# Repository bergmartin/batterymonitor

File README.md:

# ESP32 Battery Voltage Monitor

A PlatformIO project for monitoring 12V battery voltage using an ESP32 microcontroller with **ultra-low power consumption** through deep sleep mode.

## 🌟 Key Features

- **Ultra-Low Power:** Deep sleep mode with only 0.12-0.23 mA average draw (99.8% power reduction!)
- **Long Battery Life:** Monitor can run for years on the battery it's monitoring
- **MQTT Integration:** Publish readings to MQTT broker for remote monitoring (Home Assistant, Node-RED, etc.)
- **OLED Display:** SH1106 128x64 display shows battery voltage, percentage, status, and WiFi signal strength
- Real-time 12V battery voltage monitoring
- Support for **Lead-Acid** and **LiFePO4** battery types
- Battery type configured at build time
- Battery percentage calculation with type-specific thresholds
- Battery status indicators (FULL, GOOD, LOW_BATTERY, CRITICAL, DEAD)
- Visual battery level display with progress bar
- WiFi signal strength indicator
- Low battery warnings
- Averaged ADC readings for accuracy
- RTC memory for persistent data across sleep cycles
- **3D Printable Enclosure** for professional deployment

## ⚡ Power Consumption

| Mode | Current Draw | Battery Life (100Ah) |
|------|-------------|---------------------|
| **Deep Sleep (default)** | 0.12-0.23 mA | **50-95 years** 🎉 |
| Continuous monitoring | 80-160 mA | 26-52 days |

**Deep sleep mode draws less power than the battery loses naturally!**

See [DEEP_SLEEP.md](doc/DEEP_SLEEP.md) for detailed power analysis.

## Hardware Requirements

### Components
- ESP32 development board
- 12V battery
- 100kΩ resistor (R1)
- 22kΩ resistor (R2)
- SH1106 OLED Display (128x64, I2C) - optional but recommended
- Connecting wires

### Circuit Diagram

```
12V Battery (+) ----[100kΩ]----+----[22kΩ]---- GND
                               |
                          GPIO34 (ADC)
                          ESP32
```

### Voltage Divider Explanation

The ESP32 ADC can only read voltages up to 3.3V. To safely measure a 12V battery (and up to 14.6V for LiFePO4), we use a voltage divider:

- **R1** (100kΩ) + **R2** (22kΩ) creates a 5.55:1 ratio
- 12V battery voltage becomes ~2.16V at the ADC pin
- Formula: `V_ADC = V_Battery × (R2 / (R1 + R2))`
- Result: `V_ADC = 12V × (22kΩ / 122kΩ) = 2.16V`

## Wiring Instructions

1. **Connect Voltage Divider:**
   - Solder 100kΩ resistor (R1) to battery positive terminal
   - Connect 22kΩ resistor (R2) between the junction and GND
   - Connect junction point to GPIO34 on ESP32

2. **Ground Connection:**
   - Connect battery negative terminal to ESP32 GND

3. **Power ESP32:**
   - Power the ESP32 via USB or separate power supply
   - **Important:** Do NOT power ESP32 directly from the 12V battery without a voltage regulator

## Software Setup

### Installation

1. Install [PlatformIO](https://platformio.org/)
2. Clone or download this project
3. Open the project in VS Code with PlatformIO extension

### MQTT Configuration (Optional)

To enable remote monitoring via MQTT:

1. **Configure WiFi credentials:**
   ```bash
   cd include/
   cp wifi_credentials.h.example wifi_credentials.h
   # Edit wifi_credentials.h with your WiFi SSID and password
   ```

2. **Configure MQTT broker:**
   ```bash
   cp mqtt_credentials.h.example mqtt_credentials.h
   # Edit mqtt_credentials.h with your MQTT broker details
   ```

3. **See [MQTT.md](doc/MQTT.md) for complete MQTT setup guide**, including:
   - MQTT broker options (Mosquitto, CloudMQTT, Home Assistant)
   - Topic structure and JSON format
   - Home Assistant integration
   - Testing and troubleshooting

### Build and Upload

**Default (Lead-Acid battery):**
```bash
# Build the project
pio run

# Upload to ESP32
pio run --target upload

# Monitor serial output
pio device monitor
```

**For LiFePO4 battery:**
```bash
# Build for LiFePO4
pio run -e esp32dev -D BATTERY_TYPE=BATTERY_TYPE_LIFEPO4

# Upload to ESP32
pio run -e esp32dev -D BATTERY_TYPE=BATTERY_TYPE_LIFEPO4 --target upload

# Monitor serial output
pio device monitor
```

**Alternative: Edit platformio.ini**

Change the build flag in the default `[env:esp32dev]` section:
```ini
build_flags = 
  -D BATTERY_TYPE=BATTERY_TYPE_LIFEPO4  ; Options: BATTERY_TYPE_LEAD_ACID or BATTERY_TYPE_LIFEPO4
```

Or use PlatformIO IDE buttons in VS Code.

## Testing

The project includes comprehensive unit tests for all battery monitoring logic.

### Run Tests

**Test Lead-Acid configuration:**
```bash
pio test -e esp32dev
```

**Test LiFePO4 configuration:**
```bash
pio test -e esp32dev -D BATTERY_TYPE=BATTERY_TYPE_LIFEPO4
```

**Test both configurations:**
```bash
pio test
```

The tests cover:
- Battery percentage calculations
- Battery status determination
- ADC to voltage conversion
- Voltage divider safety
- Edge cases and boundary conditions

See `test/README.md` for detailed testing documentation.

## Configuration

### Battery Type Selection

The project supports two battery types, configured at **build time**:

**Option 1: Use the default environment with build flag**
- `esp32dev` with default `BATTERY_TYPE_LEAD_ACID` build flag
- `esp32dev` with `-D BATTERY_TYPE=BATTERY_TYPE_LIFEPO4` build flag for LiFePO4

**Option 2: Edit the default environment**

In `platformio.ini`, modify the build_flags:
```ini
[env:esp32dev]
build_flags = 
  -D BATTERY_TYPE=LEAD_ACID  ; or LIFEPO4
```

### Voltage Thresholds

The voltage thresholds are automatically set based on battery type:

**Lead-Acid (12V):**
- Full: 12.7V
- Nominal: 12.4V (75%)
- Low: 12.0V (25%)
- Critical: 11.8V
- Minimum: 10.5V

**LiFePO4 (12V nominal, 4S configuration):**
- Full: 14.6V
- Nominal: 13.2V (75%)
- Low: 12.8V (25%)
- Critical: 12.0V
- Minimum: 10.0V

### Other Adjustable Parameters

You can adjust these parameters in `lib/BatteryMonitor/battery_config.h` (in the `Config` namespace):

```cpp
constexpr int BATTERY_ADC_PIN = 34;           // ADC pin (GPIO34)
constexpr float VOLTAGE_DIVIDER_RATIO = 5.545;  // Adjust if using different resistors
constexpr unsigned long READING_INTERVAL_MS = 10000;  // Reading interval (active mode, 10 seconds)
constexpr uint64_t DEEP_SLEEP_INTERVAL_US = 3600000000ULL;  // Deep sleep interval (1 hour)
```

### For Different Resistor Values

If you use different resistors, calculate the voltage divider ratio:

```
VOLTAGE_DIVIDER_RATIO = (R1 + R2) / R2
```

Example:
- R1 = 100kΩ, R2 = 33kΩ → Ratio = 4.03
- R1 = 20kΩ, R2 = 10kΩ → Ratio = 3.0

## Serial Output Example

**Lead-Acid Battery:**
```
=================================
ESP32 Battery Voltage Monitor
=================================
Battery Type: Lead-Acid
Voltage Range: 10.5V - 12.7V

─────────────────────────────────
Battery Voltage: 12.45 V
Battery Level:   88.6 %
Status:          GOOD
Battery: [████████░░]
```

**LiFePO4 Battery:**
```
=================================
ESP32 Battery Voltage Monitor
=================================
Battery Type: LiFePO4
Voltage Range: 10.0V - 14.6V

─────────────────────────────────
Battery Voltage: 13.84 V
Battery Level:   83.5 %
Status:          GOOD
Battery: [████████░░]
```

## Battery Voltage Guidelines

The project automatically configures voltage thresholds based on your battery type selection.

### Lead-Acid Batteries (12V)
- **12.7V** - Fully charged (100%)
- **12.4V** - 75% charged
- **12.2V** - 50% charged
- **12.0V** - 25% charged
- **11.8V** - Discharged (should recharge)
- **10.5V** - Minimum safe voltage

### LiFePO4 Batteries (12V nominal, 4S configuration)
- **14.6V** - Fully charged (100%) - 4 × 3.65V
- **13.6V** - 90% charged
- **13.2V** - 75% charged
- **13.0V** - 50% charged
- **12.8V** - 25% charged
- **12.0V** - Discharged (should recharge)
- **10.0V** - Minimum safe voltage - 4 × 2.5V

**Note:** LiFePO4 batteries have a flatter discharge curve than lead-acid, maintaining voltage better under load.

## Safety Notes

⚠️ **Important Safety Information:**

1. **Never exceed ADC input voltage:** Ensure your voltage divider outputs max 3.0V
2. **Double-check connections:** Incorrect wiring can damage your ESP32
3. **Use proper resistor wattage:** 1/4W resistors are typically sufficient
4. **Battery polarity:** Connect positive to R1, negative to GND
5. **Isolated ground:** If powering ESP32 separately, ensure common ground with battery

## Calibration

For more accurate readings, you can calibrate the system:

1. Measure actual battery voltage with a multimeter
2. Compare with ESP32 reading
3. Adjust the `VOLTAGE_DIVIDER_RATIO` constant if needed
4. The ADC may have slight variations; fine-tune the ratio for accuracy

## Troubleshooting

**Reading shows 0V:**
- Check voltage divider connections
- Verify GPIO34 is connected to the junction point
- Check resistor values

**Reading too high/low:**
- Verify resistor values (use multimeter)
- Recalculate voltage divider ratio
- Check for loose connections

**Unstable readings:**
- Increase SAMPLES count for more averaging
- Add a small capacitor (0.1µF) across R2
- Check for electromagnetic interference

**MQTT not connecting:**
- See [MQTT.md](doc/MQTT.md) troubleshooting section
- Verify WiFi credentials in `include/wifi_credentials.h`
- Check MQTT broker is accessible and credentials are correct
- Test broker with mosquitto-clients: `mosquitto_sub -h broker -t "#"`

## Documentation

- **[WIRING.md](doc/WIRING.md)** - Detailed wiring instructions with buck converter setup
- **[DISPLAY.md](doc/DISPLAY.md)** - SH1106 OLED display wiring and configuration
- **[DEEP_SLEEP.md](doc/DEEP_SLEEP.md)** - Deep sleep implementation and power analysis
- **[MQTT.md](doc/MQTT.md)** - MQTT setup, configuration, and integration guide
- **[OTA.md](doc/OTA.md)** - Over-the-Air update setup and usage
- **[REFACTORING.md](doc/REFACTORING.md)** - Code structure and refactoring documentation
- **[AGENTS.md](doc/AGENTS.md)** - AI assistant context and best practices
- **[test/README.md](test/README.md)** - Testing framework and test documentation
- **[enclosure/README.md](enclosure/README.md)** - 3D printable enclosure guide

## License

MIT License - Feel free to modify and use in your projects.

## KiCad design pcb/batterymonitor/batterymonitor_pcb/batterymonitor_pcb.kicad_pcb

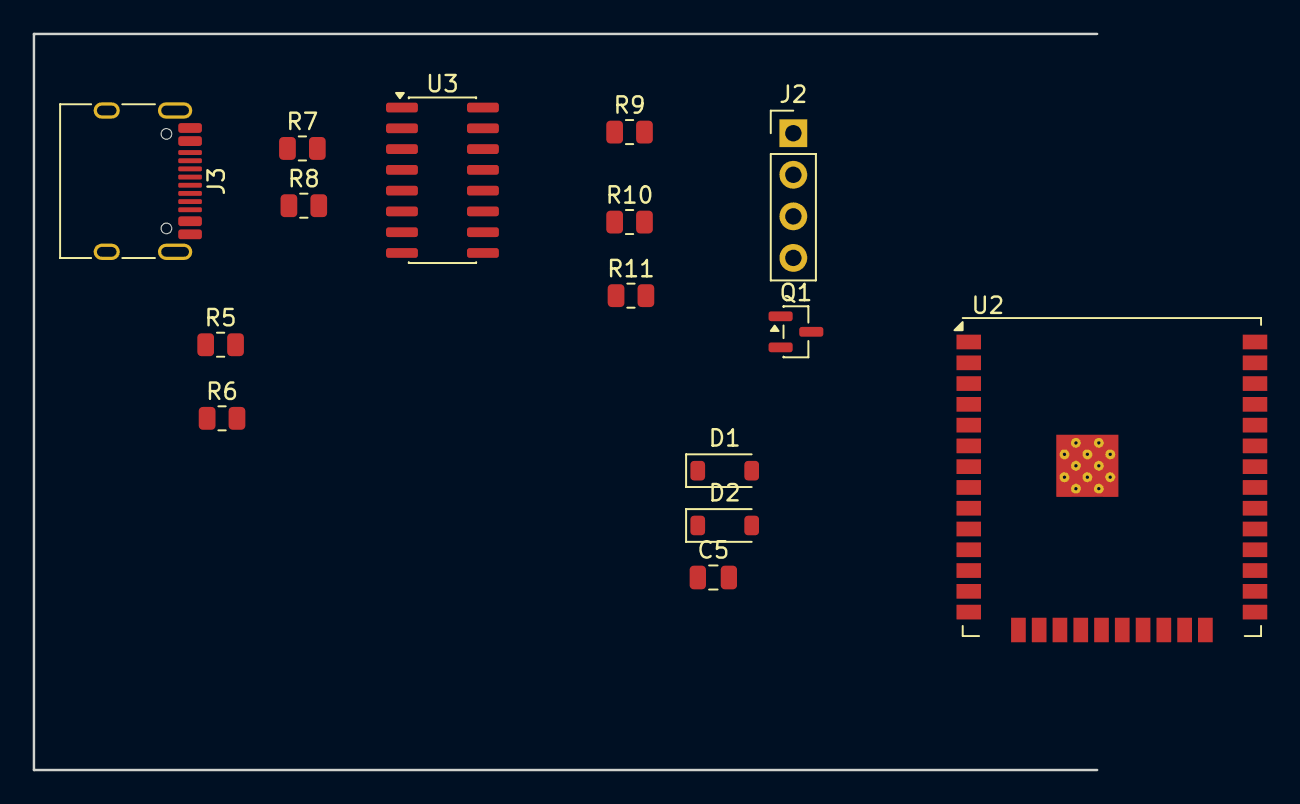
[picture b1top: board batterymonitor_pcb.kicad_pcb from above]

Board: 2 copper layers, 65.0 x 45.0 mm, 15 parts (0 on the bottom side), 17 nets, no tracks yet.

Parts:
C5: 100nF/10V; C_0805_2012Metric
D1, D2: SS14; D_SOD-123
J2: Conn_01x04_Pin; PinHeader_1x04_P2.54mm_Vertical
J3: USB_C_Receptacle_HRO_TYPE-C-31-M-12
Q1: S8050; SOT-23
R5, R6: 1k; R_0805_2012Metric
R7, R8: 5.1k; R_0805_2012Metric
R9, R10, R11: 10k; R_0805_2012Metric
U2: ESP32-WROOM-32U-N4; ESP32-WROOM-32U
U3: CH340C; SOIC-16_3.9x9.9mm_P1.27mm

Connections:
/3.3V: C5.1, J2.1, R11.1, U2.2 (3V3), U3.5 (VCC), U3.6 (V3)
/12V: D1.1 (K), D2.1 (K)
/ESP_EN: Q1.3 (C), R11.2, U2.3 (EN)
/ESP_RXD: R5.2, U2.34 (RXD0)
/ESP_TXD: R6.1, U2.35 (TXD0), U3.8 (RXD)
/GND: C5.2, J2.2, J3.A1 (GND), J3.B12 (GND), J3.SH (SHIELD), R7.2, R8.2, U2.1 (GND), U2.15 (GND), U2.38 (GND), U3.3 (GND)
/SCL: J2.3, U2.36 (GPIO22)
/SDA: J2.4, U2.33 (GPIO21)
/USB_CC1: J3.A5 (CC1), R7.1
/USB_CC2: J3.B5 (CC2), R8.1
/USB_DN: J3.A7 (D-), J3.B7 (D-), U3.2 (UD-)
/USB_DP: J3.A6 (D+), J3.B6 (D+), U3.1 (UD+)
/USB_DTR: Q1.2 (E), R10.2, U3.9 (DTR)
/USB_RTS: R9.2, U3.14 (RTS)
/VBUS: D2.2 (A), J3.A4 (VBUS), J3.B9 (VBUS)
unnamed: Q1.1 (B), R9.1
unnamed: R5.1, U3.7 (TXD)

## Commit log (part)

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2025-12-09 Add ESP32 battery monitor with Lead-Acid and LiFePO4 support
2025-12-10 Add comprehensive unit tests and refactor code into library
    - Created BatteryMonitor library with battery_monitor.h/cpp
    - Refactored shared functions (calculateBatteryPercentage, getBatteryStatus, adcToBatteryVoltage)
    - Added 32 unit tests covering:
    - Battery percentage calculations
    - Battery status determination
    - ADC to voltage conversion
2025-12-10 Add comprehensive refactoring documentation
2025-12-11 Update README with deep sleep power features
    Highlight ultra-low power consumption in main README:
    - Power consumption comparison table
    - Link to detailed DEEP_SLEEP.md documentation
    - Emphasize power efficiency as key feature
2025-12-11 Add comprehensive wiring guide and hardware documentation
    Complete hardware setup documentation:
    - Detailed wiring diagrams with ASCII art
    - Component list with specifications
    - Step-by-step connection instructions
    - Pin configuration reference
    - Wire gauge recommendations
2025-12-11 adding satl files to gitignore
2025-12-13 Add MQTT publishing for remote battery monitoring
    Implemented MQTT functionality to publish battery readings to an MQTT broker:
    Features:
    - WiFi connection with configurable timeout
    - MQTT client using PubSubClient library
    - Publishes voltage, percentage, status, type, boot count
    - JSON topic with all data + WiFi RSSI
2025-12-13 Update config and MQTT publishing logic
    - Tweak WiFi/MQTT timeouts and configuration in battery_config.h
    - Adjust MQTT publish flow in main.cpp for reliability and power
    - Prep for remote monitoring with retained JSON payloads
2025-12-13 remove useless readme files
2025-12-15 feat: serial deep-sleep controls and first-boot delay
    - Add serial commands: 'nosleep'/'sleep' and 'set deep_sleep <on|off>'
    - Persist deep sleep setting in NVS via ConfigManager
    - Wait 30s before first deep sleep to allow serial config
    - Update release workflow notes re: NVS defaults
    - Update VS Code includes for ConfigManager/Preferences
2025-12-15 refactor: extract manager classes for better separation of concerns
    - Create NetworkManager class (224 lines)
    - WiFi and MQTT connection management
    - Callback system for OTA and reset triggers
    - Publishing and disconnect handling
    - Create OTAManager class (214 lines)
    - ArduinoOTA and HTTP update handling
2025-12-15 refactor: separate manager implementations from headers
    - Split NetworkManager into network_manager.h (38 lines) and network_manager.cpp (213 lines)
    - Split OTAManager into ota_manager.h (36 lines) and ota_manager.cpp (210 lines)
    - Split CommandHandler into command_handler.h (24 lines) and command_handler.cpp (205 lines)
    - Follows C++ best practices for interface/implementation separation
    - Improves compilation times (changes to .cpp don't require recompiling dependents)
    - Maintains all functionality with cleaner, more maintainable code structure
2025-12-16 feat: Add DHCP support, persistent OTA triggers, and automatic update checking
    - Switch from static IP to DHCP by default (configurable via USE_STATIC_IP flag)
    - Implement persistent OTA trigger storage across deep sleep cycles using ESP32 Preferences
    - Add automatic version checking on every wake cycle
    - Firmware now checks GitHub for newer versions and auto-updates when available
    - OTA updates triggered via MQTT are now persisted and processed on next boot
    - Add version tracking (FIRMWARE_VERSION) and configurable OTA_VERSION_URL
2025-12-16 bring version number back to 1.0.0
2025-12-16 refactor: Replace version.txt URL check with config-based OTA target version
    - Remove automatic version.txt fetching from URL
    - Add otaTargetVersion to ConfigManager (persisted in NVS)
    - Update checkForUpdates() to use configured target version instead of fetching
    - Add 'otaver' serial command to set OTA target version
    - Version checking now controlled via local config instead of remote file
    - Simpler and more predictable OTA behavior
2025-12-16 feat: Show passwords in plaintext when displaying config via serial
2025-12-16 fix: Include battery type in automatic OTA firmware filename
    - OTA manager now constructs filename as firmware-leadacid-v1.0.2.bin
    - Matches the naming convention from GitHub release workflow
    - Automatically detects BATTERY_TYPE (LEAD_ACID or LIFEPO4) at compile time
    - Ensures correct firmware variant is downloaded for each device type
2025-12-16 docs: Fix release workflow documentation to use new OTA URL structure
    - Update firmware file references from versioned names to simple names
    - Update MQTT examples to use version in path: v1.0.2/firmware-leadacid.bin
    - Remove outdated version.txt references
    - Clarify otaver command usage for setting target version
2025-12-16 fix: Use WiFiClientSecure for HTTPS OTA downloads
    - Changed from WiFiClient to WiFiClientSecure for GitHub HTTPS URLs
    - Add setInsecure() to skip certificate verification
    - Fixes 'connection lost' error when downloading from GitHub
    - GitHub requires HTTPS and proper TLS client
2025-12-16 fix: Add redirect handling for GitHub OTA downloads
    - Add setFollowRedirects(HTTPC_FORCE_FOLLOW_REDIRECTS) to handle 302 redirects
    - Set 30 second timeout for large firmware downloads
    - Fixes HTTP Code 302 error from GitHub CDN
2025-12-16 small fixes
2025-12-16 fix: Set default firmware version to 'dev' for local builds
2025-12-16 fix: Remove setTimeout call - HTTPUpdate doesn't have this method
2025-12-16 fix: Prevent OTA loop by ignoring empty MQTT messages
    - Empty messages are used only to clear retained flag
    - Don't trigger OTA callback on empty message
    - Prevents infinite loop when clear message triggers callback
    - Restructured logic for better clarity
2025-12-16 feat: Add clearota command to manually clear pending OTA triggers
    - Add 'clearota' serial command to clear pending OTA from preferences
    - Helps break OTA update loops
    - Expose clearOTATrigger as public method in OTAManager
    - Update help text with new command
2025-12-16 feat: Add hostname and firmware version to MQTT payload
    - Publish hostname to battery/monitor/hostname topic
    - Publish firmware version to battery/monitor/version topic
    - Include both in JSON payload
    - Helps identify device and track deployed firmware versions
2025-12-16 feat: Use WiFi hostname instead of MQTT client ID in payload
    - Set WiFi hostname using MQTT client ID on connect
    - Use WiFi.getHostname() for published hostname value
    - Ensures network hostname matches published identifier
2025-12-16 refactor: Use only Home Assistant MQTT topics
    - Remove legacy battery/monitor/* topics
    - Publish only to homeassistant/sensor/<hostname>/*/state topics
    - Cleaner topic structure following HA conventions
    - All sensors under homeassistant/ namespace
2025-12-16 config: Change deep sleep interval to 2 minutes
    - Reduced from 4 hours to 2 minutes for more frequent updates
    - DEEP_SLEEP_INTERVAL_US = 120000000 microseconds (2 minutes)
2025-12-16 refactor: Use device-based MQTT discovery with single state topic
    - Publish one JSON payload to homeassistant/sensor/<hostname>/state
    - All sensors use value_template to extract from same JSON
    - More efficient: 1 MQTT message instead of 6
    - Reduces network traffic and broker load
    - All sensors still properly grouped under device
2025-12-17 Add firmware version sensor
    - Publish firmware version to <hostname>_firmware/state topic
    - Add discovery config with diagnostic entity_category
    - Use FIRMWARE_VERSION macro or 'dev' as fallback
2025-12-17 feat(config): runtime battery chemistry via NVS and MQTT\n\n- Add to ConfigManager stored in NVS\n- Refactor BatteryMonitor to use runtime chemistry with dynamic thresholds\n- Set chemistry from NVS 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
2025-12-18 fix: resolve macro collision between LEAD_ACID/LIFEPO4 and enum values
    - Rename preprocessor macros from LEAD_ACID/LIFEPO4 to BATTERY_TYPE_LEAD_ACID/BATTERY_TYPE_LIFEPO4 to prevent collision with BatteryChemistry enum values
    - Update all #if/#elif preprocessor checks in battery_config.h, ota_manager.cpp, and test_battery_monitor.cpp
    - Update platformio.ini build flags to use renamed macros
    - Update error message to reference new macro names
    - Update VS Code C++ properties to use new macro names
    This fixes compile errors 'expected an identifier' when using BatteryChemistry::LEAD_ACID and BatteryChemistry::LIFEPO4 in conditional compilation.
2025-12-19 Set deep sleep to 1h and shorten WiFi timeout
2025-12-21 fix: correct documentation for PlatformIO environments and configurations
    - Remove references to nonexistent esp32dev-leadacid and esp32dev-lifepo4 environments
    - Update build instructions to use esp32dev with BATTERY_TYPE build flags
    - Correct configuration documentation to reference battery_config.h instead of src/main.cpp
    - Fix parameter names to use Config namespace (BATTERY_ADC_PIN, READING_INTERVAL_MS, etc)
    - Correct DEEP_SLEEP.md power calculations (reverse best/worst case years)
    - Update daily consumption from 2.9-5.5 to 2.9-5.6 mAh
2026-01-07 docs: add guidelines for AI agents and developers in AGENTS.md
2026-01-07 docs: update MQTT setup guide link in README.md
2026-01-07 docs: restore and enhance guidelines for AI agents and developers in AGENTS.md
2026-01-07 feat: add OTA update display functionality with progress and error handling
2026-01-08 feat: enhance sleep screen to display last battery reading information
2026-01-09 feat: update sleep screen to display next reading time with improved formatting
2026-01-09 feat: update NetworkManager to use WiFiClientSecure for secure MQTT connections
2026-01-09 Add CI/CD for nightly builds and automatic OTA deployment
    - Add scheduled nightly builds (2 AM UTC daily)
    - Add workflow_dispatch for manual triggers
    - Enforce tags can only be created on main branch
    - Add automatic OTA deployment via MQTT when tags are pushed
    - Nightly builds stored as artifacts (30 day retention)
    - Tag builds create GitHub releases with OTA trigger
2026-01-09 Change nightly builds to trigger on branch pushes
    - Remove scheduled nightly builds (cron)
    - Build on all branch pushes for continuous testing
    - Tag pushes still create releases and trigger OTA
    - Keeps manual workflow_dispatch trigger
2026-01-09 Add production environment configuration for firmware builds
2026-01-09 Rename workflow from "Build and Release Firmware" to "Release Firmware"
2026-01-09 Fix OTA URL construction for production firmware releases
2026-01-10 Fix constant reboot loop by using infinite loop when nosleep enabled
    Problem: When deep sleep was disabled with nosleep command, the loop()
    function would finish and restart, causing the device to:
    - Reconnect to WiFi on every iteration
    - Reconnect to MQTT on every iteration
    - Take new readings and publish repeatedly
    - Never properly listen for commands
2026-05-13 feat: implement appliance relay management with battery protection
    The appliance can now be controlled via MQTT and is automatically forced OFF if the battery voltage falls below a safety threshold. Features include:
    - Hysteresis (cutoff vs recovery thresholds) to prevent relay chatter
    - Persistence of target state in NVS
    - State retention across deep sleep using RTC GPIO hold
    - Home Assistant MQTT Discovery integration as a Switch entity
2026-06-02 Fix syntax and parsing errors in KiCad PCB layout
2026-06-02 Implement AP63300 buck converter design in PCB and schematic
2026-06-02 Update wiring and enclosure documentation with AP63300 PCB design details
2026-06-12 Add DC Jack Female component to BOM files for battery monitor PCB
    - Added DC Jack Female (J4) to both bom_jlcpcb.csv and bom_pcbway.csv
    - Updated component details including footprint and manufacturer information
